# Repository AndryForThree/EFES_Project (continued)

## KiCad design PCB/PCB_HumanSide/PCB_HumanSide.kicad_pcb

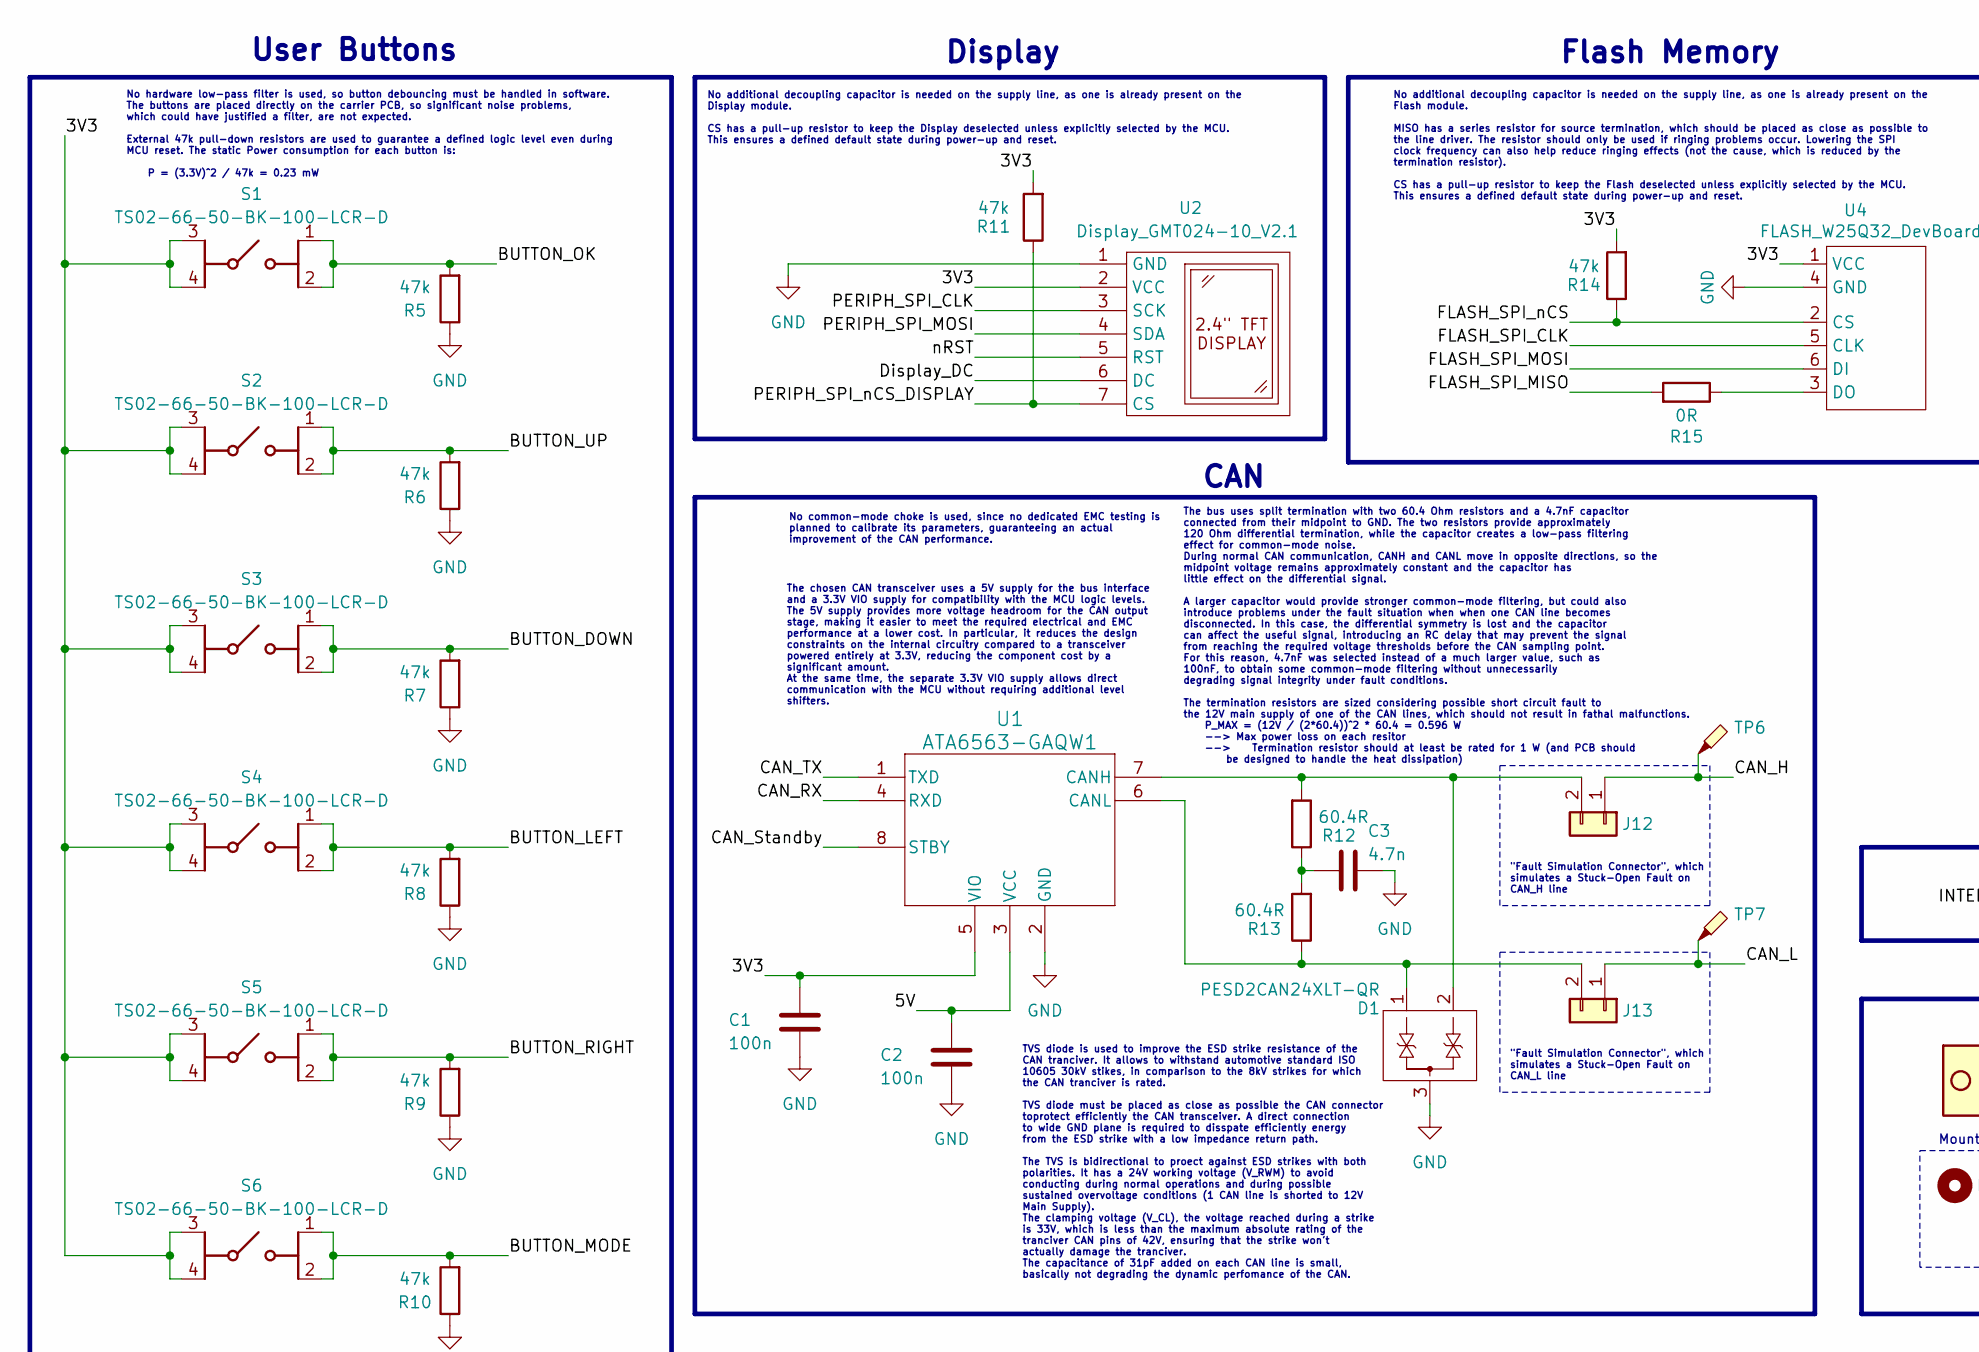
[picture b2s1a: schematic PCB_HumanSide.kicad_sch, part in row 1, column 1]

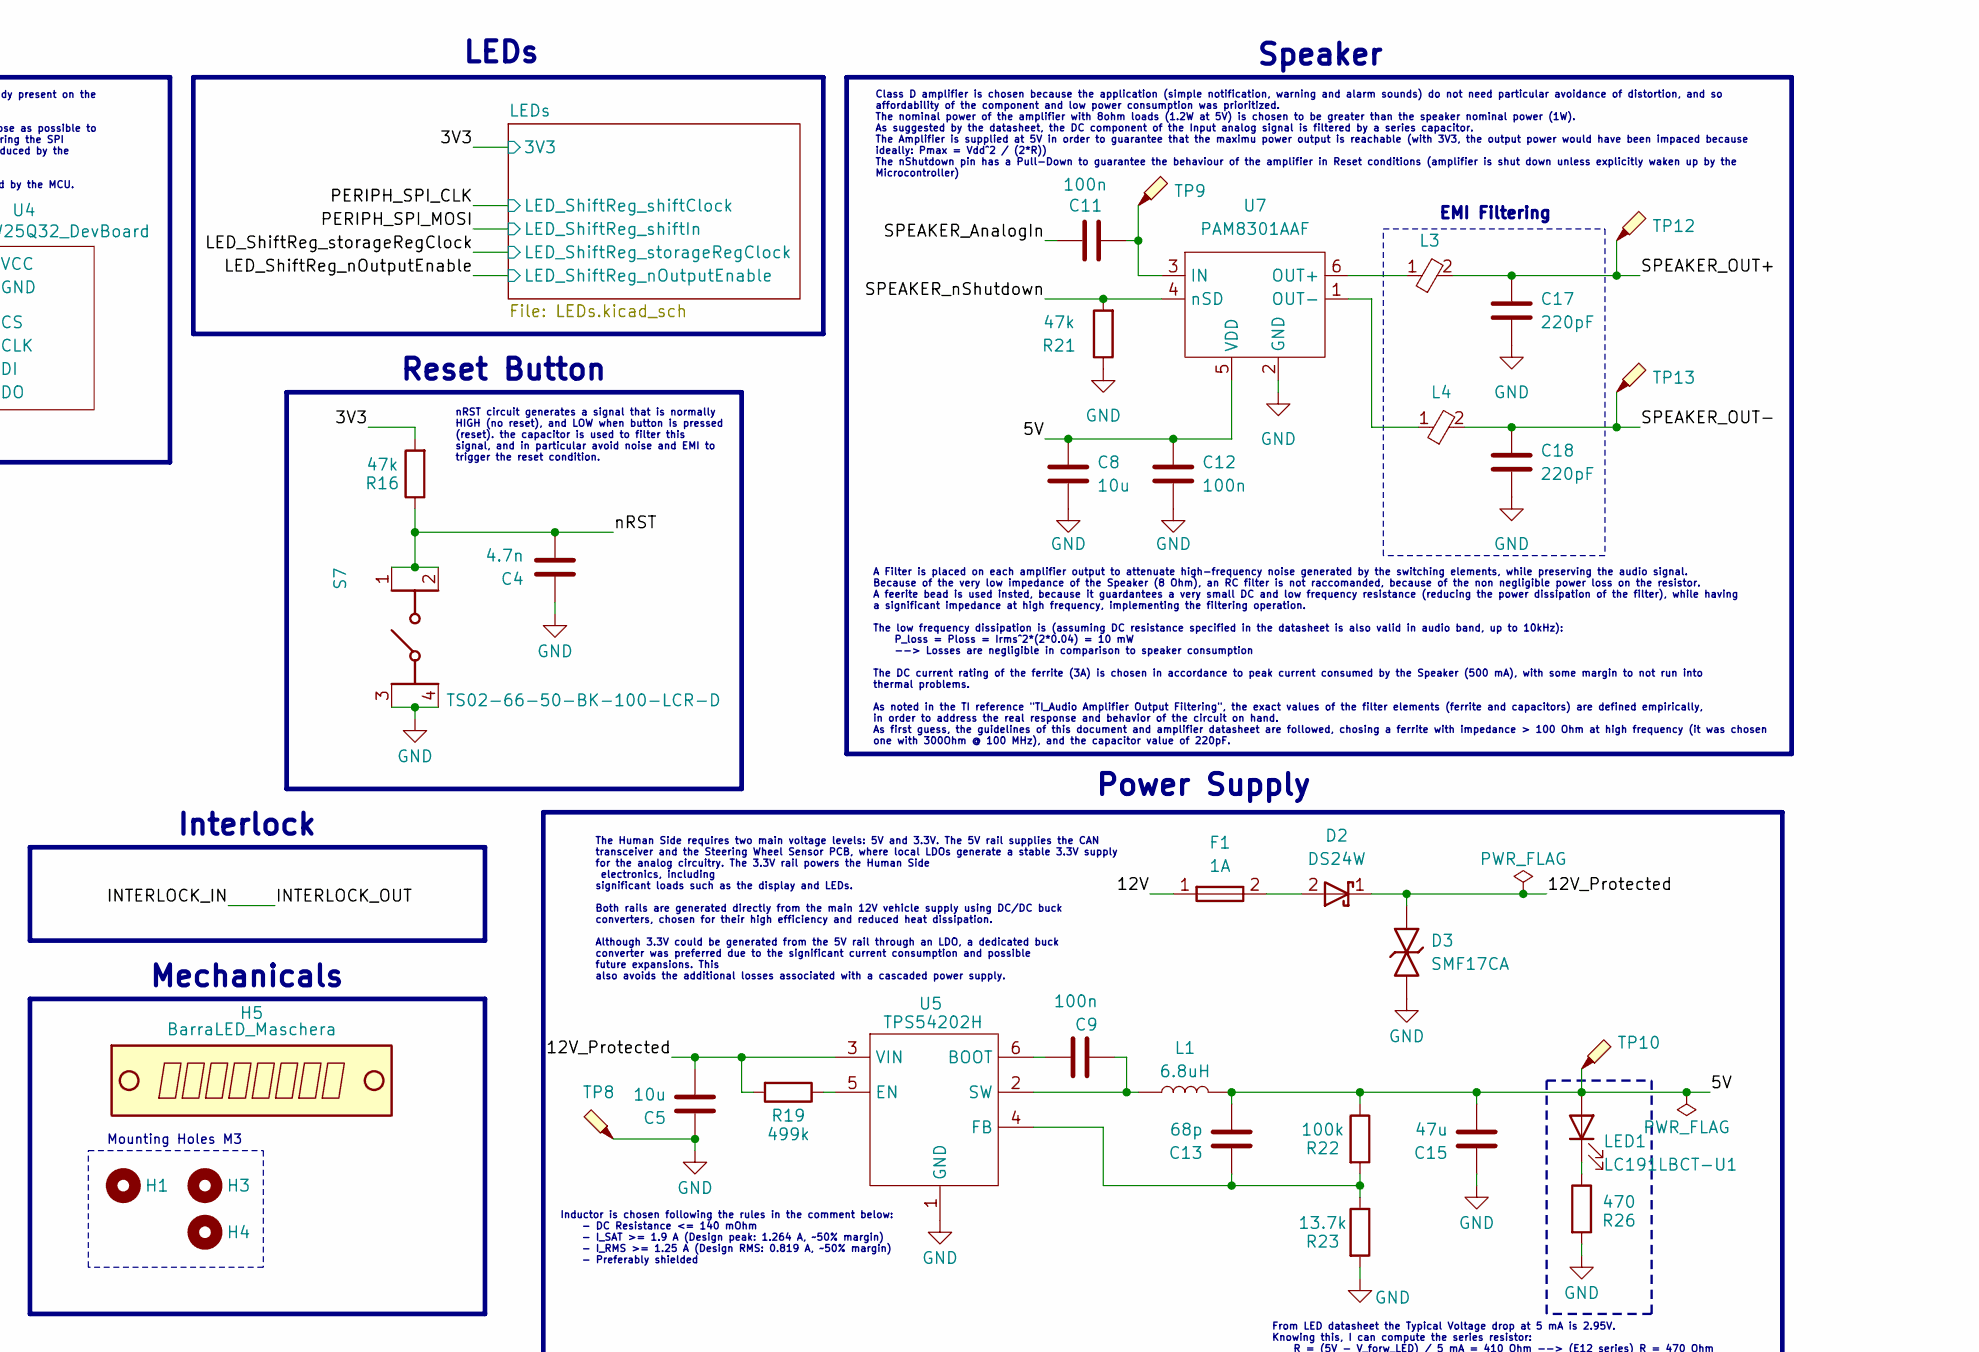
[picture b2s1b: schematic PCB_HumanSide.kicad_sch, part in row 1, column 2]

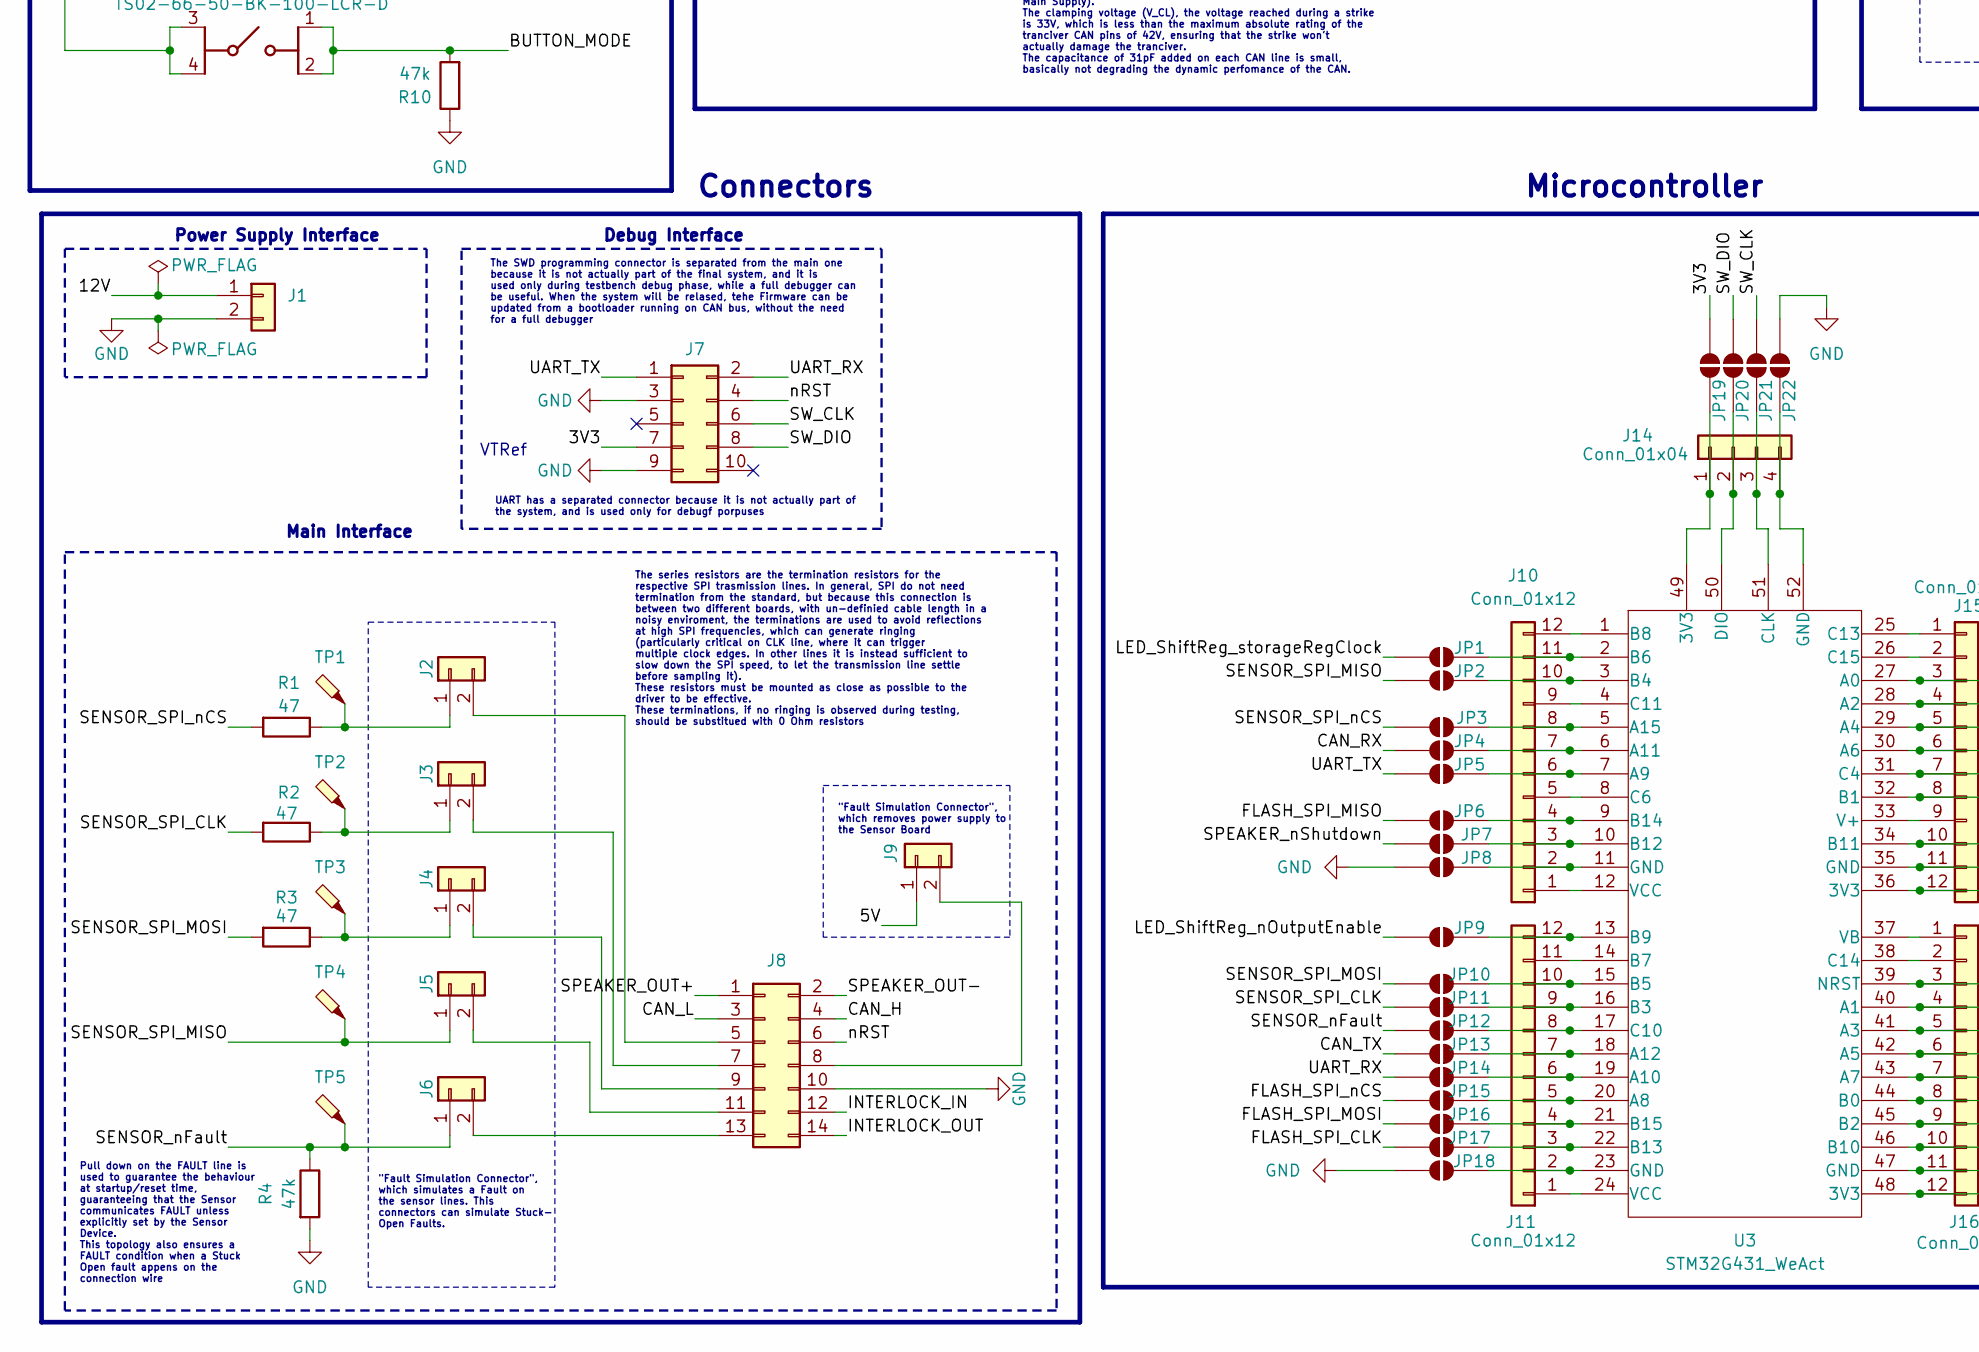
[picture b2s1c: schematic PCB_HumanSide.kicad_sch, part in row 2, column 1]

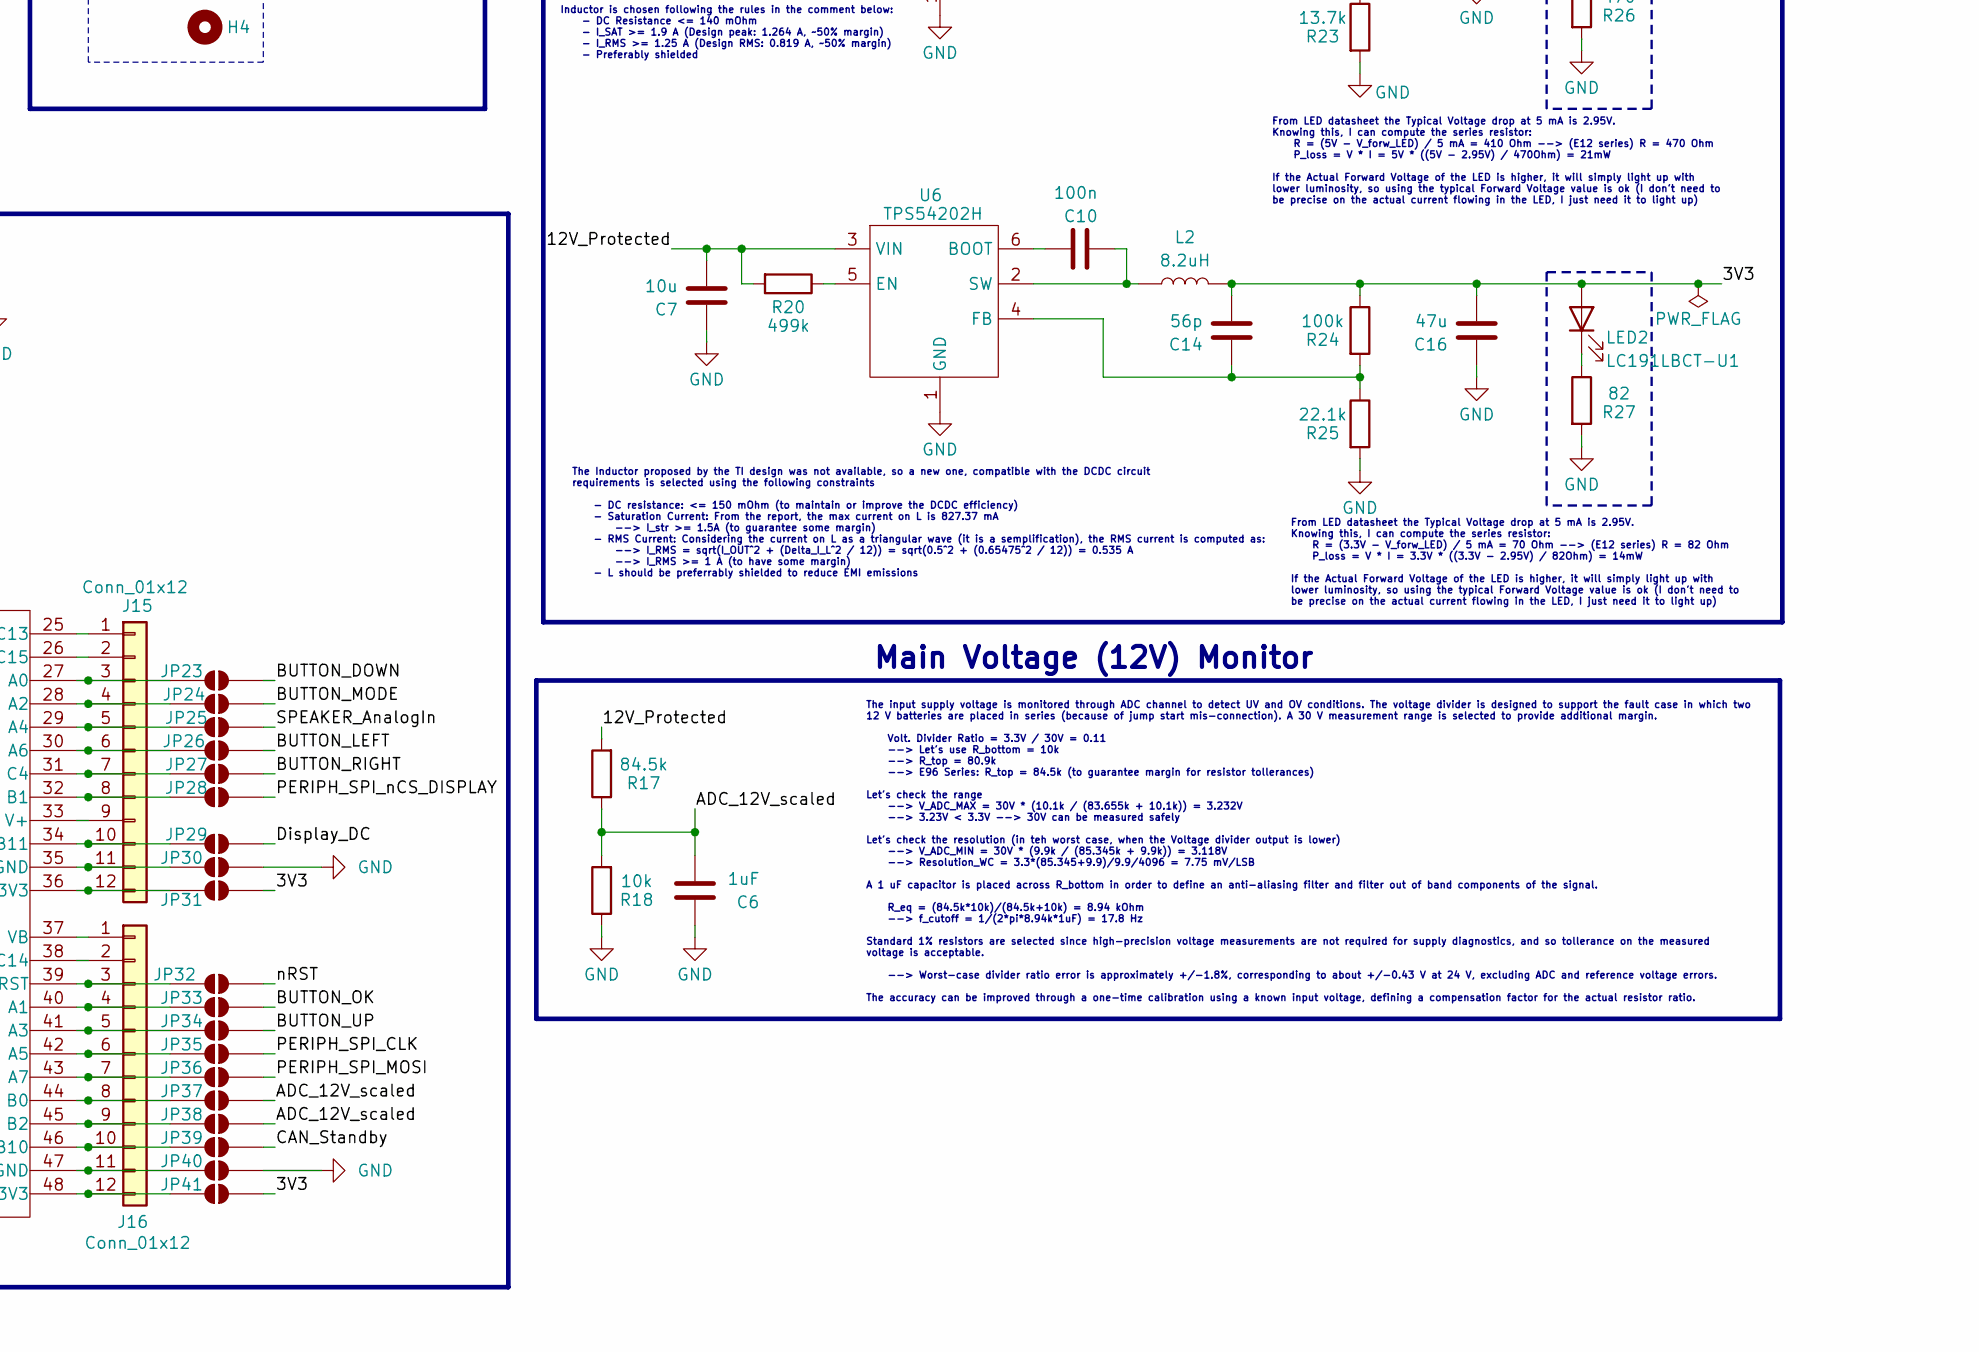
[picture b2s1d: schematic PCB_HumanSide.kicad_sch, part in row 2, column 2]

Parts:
C1, C2, C9, C10, C11, C12: 100n; C_0805_2012Metric_Pad1.18x1.45mm_HandSolder
C3, C4: 4.7n; C_0805_2012Metric_Pad1.18x1.45mm_HandSolder
C5, C7: 10u; C_1206_3216Metric_Pad1.33x1.80mm_HandSolder
C6: 1uF; C_0805_2012Metric_Pad1.18x1.45mm_HandSolder
C8: 10u; C_0805_2012Metric_Pad1.18x1.45mm_HandSolder
C13: 68p; C_0805_2012Metric_Pad1.18x1.45mm_HandSolder
C14: 56p; C_0805_2012Metric_Pad1.18x1.45mm_HandSolder
C15, C16: 47u; C_1206_3216Metric_Pad1.33x1.80mm_HandSolder
C17, C18: 220pF; C_0805_2012Metric_Pad1.18x1.45mm_HandSolder
D1: PESD2CAN24XLT-QR; SOT-23
D2: DS24W; SOD-123_HandSolder
D3: SMF17CA; SOD-123_Bidirectional_HandSolder
F1: 1A; Fuse_1206_3216Metric_Pad1.42x1.75mm_HandSolder
H1, H3, H4: MountingHole; MountingHole_3.2mm_M3
H5: BarraLED_Maschera
J1: TAD05-02-1-L-G; CONN_TAD05-02-1-L-G
J2, J3, J4, J5, J6: Conn_01x03; PinHeader_1x02_P2.54mm_Vertical
J7: SBH11-PBPC-D05-RA-BK; CONN_SBH11-PBPC-D05-RA-BK
J8: SBH11-PBPC-D07-RA-BK; CONN_SBH11-PBPC-D07-RA-BK
J9: Conn_01x02; PinHeader_1x02_P2.54mm_Vertical
J10, J11, J15, J16: Conn_01x12; PinSocket_1x12_P2.54mm_Vertical_TightCourtyard
J12, J13: Conn_01x05; PinHeader_1x02_P2.54mm_Vertical
J14: Conn_01x04; PinSocket_1x04_P2.54mm_Vertical
JP1, JP2, JP3, JP4, JP5, JP6, JP7, JP8, JP9, JP10, JP11, JP12, JP13, JP14, JP15, JP16, JP17, JP18, JP23, JP24, JP25, JP26, JP27, JP28, JP29, JP30, JP31, JP32, JP33, JP34, JP35, JP36, JP37, JP38, JP39, JP40, JP41: SolderBride_0603
JP19, JP20, JP21, JP22: SolderJumper_2_Open; SolderBride_0603
L1: 6.8uH; INDUCT_SRP4020T-6R8M
L2: 8.2uH; INDUCT_CSHB0430R-8R2M
L3, L4: HCB2012KF-301T30; R_0805_2012Metric_Pad1.20x1.40mm_HandSolder
LED1, LED2: LC191LBCT-U1; LED_0603_HandSolder
R1, R2, R3: 47; R_0805_2012Metric_Pad1.20x1.40mm_HandSolder
R4, R5, R6, R7, R8, R9, R10, R11, R14, R16, R21: 47k; R_0805_2012Metric_Pad1.20x1.40mm_HandSolder
R12, R13: 60.4R; R_0805_2012Metric_Pad1.20x1.40mm_HandSolder
R15: 0R; R_0805_2012Metric_Pad1.20x1.40mm_HandSolder
R17: 84.5k; R_0805_2012Metric_Pad1.20x1.40mm_HandSolder
R18: 10k; R_0805_2012Metric_Pad1.20x1.40mm_HandSolder
R19, R20: 499k; R_0805_2012Metric_Pad1.20x1.40mm_HandSolder
R22, R24: 100k; R_0805_2012Metric_Pad1.20x1.40mm_HandSolder
R23: 13.7k; R_0805_2012Metric_Pad1.20x1.40mm_HandSolder
R25: 22.1k; R_0805_2012Metric_Pad1.20x1.40mm_HandSolder
R26: 470; R_0805_2012Metric_Pad1.20x1.40mm_HandSolder
R27: 82; R_0805_2012Metric_Pad1.20x1.40mm_HandSolder
S1, S2, S3, S4, S5, S6, S7: TS02-66-50-BK-100-LCR-D; BUTTON_TS0266100BK100LCRD; Manufacturer_Part_Number TS02-66-50-BK-100-LCR-D; Mouser Part Number 179-TS026650BK100LCR
TP1, TP2, TP3, TP4, TP5, TP6, TP7, TP8, TP9, TP10, TP12, TP13: TestPoint_Probe; TestPoint_Pad_1.5x1.5mm
U1: ATA6563-GAQW1; SOIC8_D_TEX-M
U2: Display_GMT024-10_V2.1
U3: STM32G431_WeAct
U4: FLASH_W25Q32_DevBoard
U5, U6: TPS54202H; SOT-23-6_DBV_TEX-M
U7: PAM8301AAF; SOT-23-6_DBV_TEX-M

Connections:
/3V3: C1.1, C14.2, C16.2, J7.7, JP19.2 (B), JP31.2 (B), JP41.2 (B), L2.2, LED2.2 (A), R11.2, R14.2, R16.2, R24.1, S1.3 (COM_1), S1.4 (COM_2), S2.3 (COM_1), S2.4 (COM_2), S3.3 (COM_1), S3.4 (COM_2), S4.3 (COM_1), S4.4 (COM_2), S5.3 (COM_1), S5.4 (COM_2), S6.3 (COM_1), S6.4 (COM_2), U1.5 (VIO), U2.2 (VCC), U4.1 (VCC); also elsewhere on the board
/5V: C2.1, C8.1, C12.1, C13.2, C15.2, J9.1, L1.2, LED1.2 (A), R22.1, TP10.1 (1_1), U1.3 (VCC), U7.5 (VDD)
/12V: F1.1, J1.1
/12V_Protected: C5.2, C7.2, D2.1 (K), D3.2 (A), R17.2, R19.2, R20.2, U5.3 (VIN), U6.3 (VIN)
/ADC_12V_scaled: C6.2, JP37.2 (B), JP38.2 (B), R17.1, R18.2
/BUTTON_DOWN: JP23.2 (B), R7.2, S3.1 (NO_1), S3.2 (NO_2)
/BUTTON_LEFT: JP26.1 (A), R8.2, S4.1 (NO_1), S4.2 (NO_2)
/BUTTON_MODE: JP24.1 (A), R10.2, S6.1 (NO_1), S6.2 (NO_2)
/BUTTON_OK: JP33.2 (B), R5.2, S1.1 (NO_1), S1.2 (NO_2)
/BUTTON_RIGHT: JP27.1 (A), R9.2, S5.1 (NO_1), S5.2 (NO_2)
/BUTTON_UP: JP34.2 (B), R6.2, S2.1 (NO_1), S2.2 (NO_2)
/CAN_H: J8.4, J12.1, TP6.1 (1_1)
/CAN_L: J8.3, J13.1, TP7.1 (1_1)
/CAN_RX: JP4.1 (A), U1.4 (RXD)
/CAN_Standby: JP39.1 (A), U1.8 (STBY)
/CAN_TX: JP13.1 (A), U1.1 (TXD)
/Display_DC: JP29.1 (A), U2.6 (DC)
/FLASH_SPI_CLK: JP17.1 (A), U4.5 (CLK)
/FLASH_SPI_MISO: JP6.1 (A), R15.2
/FLASH_SPI_MOSI: JP16.1 (A), U4.6 (DI)
/FLASH_SPI_nCS: JP15.1 (A), R14.1, U4.2 (CS)
/INTERLOCK_IN: J8.12 (Pin_10), J8.14 (Pin_10)
/LED_ShiftReg_nOutputEnable: JP9.1 (A); also elsewhere on the board
/LED_ShiftReg_storageRegClock: JP1.1 (A); also elsewhere on the board
/PERIPH_SPI_CLK: JP35.2 (B), U2.3 (SCK); also elsewhere on the board
/PERIPH_SPI_MOSI: JP36.2 (B), U2.4 (SDA); also elsewhere on the board
/PERIPH_SPI_nCS_DISPLAY: JP28.1 (A), R11.1, U2.7 (CS)
/SENSOR_SPI_CLK: JP11.1 (A), R2.2
/SENSOR_SPI_MISO: J5.1, JP2.1 (A), TP4.1 (1_1)
/SENSOR_SPI_MOSI: JP10.1 (A), R3.2
/SENSOR_SPI_nCS: JP3.1 (A), R1.2
/SENSOR_nFault: J6.1, JP12.1 (A), R4.1, TP5.1 (1_1)
/SPEAKER_AnalogIn: C11.1, JP25.1 (A)
/SPEAKER_OUT+: C17.1, J8.1, L3.2, TP12.1 (1_1)
/SPEAKER_OUT-: C18.1, J8.2, L4.2, TP13.1 (1_1)
/SPEAKER_nShutdown: JP7.2 (B), R21.2, U7.4 (nSD)
/SW_CLK: J7.6, JP21.2 (B)
/SW_DIO: J7.8, JP20.2 (B)
/UART_RX: J7.2, JP14.1 (A)
/UART_TX: J7.1, JP5.1 (A)
/nRST: C4.2, J7.4, J8.6, JP32.2 (B), R16.1, S7.1 (NO_1), S7.2 (NO_2), U2.5 (RST)
GND: C1.2, C2.2, C3.2, C4.1, C5.1, C6.1, C7.1, C8.2, C12.2, C15.1, C16.1, C17.2, C18.2, D1.3 (COM), D3.1 (K), J1.2, J7.3, J7.9, J8.10, JP8.2 (B), JP18.2 (B), JP22.2 (B), JP30.2 (B), JP40.2 (B), R4.2, R5.1, R6.1, R7.1, R8.1, R9.1, R10.1, R18.1, R21.1, R23.2, R25.2, R26.2, R27.2, S7.3 (COM_1), S7.4 (COM_2), TP8.1 (1_1), U1.2 (GND), U2.1 (GND), U4.4 (GND), U5.1 (GND), U6.1 (GND), U7.2 (GND); also elsewhere on the board
unnamed: C3.1, R12.1, R13.2
unnamed: D1.1 (K1), J13.2, R13.1, U1.6 (CANL)
unnamed: D1.2 (K2), J12.2, R12.2, U1.7 (CANH)
unnamed: D2.2 (A), F1.2
unnamed: J2.1, R1.1, TP1.1 (1_1)
unnamed: J2.2, J8.5
unnamed: J3.1, R2.1, TP2.1 (1_1)
unnamed: J3.2, J8.7
unnamed: J4.1, R3.1, TP3.1 (1_1)
unnamed: J4.2, J8.9
unnamed: J5.2, J8.11 (Pin_9)
unnamed: J6.2, J8.13 (Pin_9)
unnamed: J8.8, J9.2
unnamed: J10.1, U3.12 (VCC)
unnamed: J10.2, JP8.1 (A), U3.11 (GND)
unnamed: J10.3, JP7.1 (A), U3.10 (B12)
unnamed: J10.4, JP6.2 (B), U3.9 (B14)
unnamed: J10.5, U3.8 (C6)
unnamed: J10.6, JP5.2 (B), U3.7 (A9)
unnamed: J10.7, JP4.2 (B), U3.6 (A11)
unnamed: J10.8, JP3.2 (B), U3.5 (A15)
unnamed: J10.9, U3.4 (C11)
unnamed: J10.10, JP2.2 (B), U3.3 (B4)
unnamed: J10.11, JP1.2 (B), U3.2 (B6)
unnamed: J10.12, U3.1 (B8)
unnamed: J11.1, U3.24 (VCC)
unnamed: J11.2, JP18.1 (A), U3.23 (GND)
unnamed: J11.3, JP17.2 (B), U3.22 (B13)
unnamed: J11.4, JP16.2 (B), U3.21 (B15)
unnamed: J11.5, JP15.2 (B), U3.20 (A8)
unnamed: J11.6, JP14.2 (B), U3.19 (A10)
unnamed: J11.7, JP13.2 (B), U3.18 (A12)
unnamed: J11.8, JP12.2 (B), U3.17 (C10)
unnamed: J11.9, JP11.2 (B), U3.16 (B3)
unnamed: J11.10, JP10.2 (B), U3.15 (B5)
unnamed: J11.11, U3.14 (B7)
unnamed: J11.12, JP9.2 (B), U3.13 (B9)
unnamed: J14.1, JP19.1 (A), U3.49 (3V3)
unnamed: J14.2, JP20.1 (A), U3.50 (DIO)
unnamed: J14.3, JP21.1 (A), U3.51 (CLK)
unnamed: J14.4, JP22.1 (A), U3.52 (GND)
unnamed: J15.1, U3.25 (C13)
unnamed: J15.2, U3.26 (C15)
unnamed: J15.3, JP23.1 (A), U3.27 (A0)
unnamed: J15.4, JP24.2 (B), U3.28 (A2)
unnamed: J15.5, JP25.2 (B), U3.29 (A4)
unnamed: J15.6, JP26.2 (B), U3.30 (A6)
unnamed: J15.7, JP27.2 (B), U3.31 (C4)
unnamed: J15.8, JP28.2 (B), U3.32 (B1)
unnamed: J15.9, U3.33 (V+)
unnamed: J15.10, JP29.2 (B), U3.34 (B11)
unnamed: J15.11, JP30.1 (A), U3.35 (GND)
unnamed: J15.12, JP31.1 (A), U3.36 (3V3)
unnamed: J16.1, U3.37 (VB)
unnamed: J16.2, U3.38 (C14)
unnamed: J16.3, JP32.1 (A), U3.39 (NRST)
unnamed: J16.4, JP33.1 (A), U3.40 (A1)
unnamed: J16.5, JP34.1 (A), U3.41 (A3)
unnamed: J16.6, JP35.1 (A), U3.42 (A5)
unnamed: J16.7, JP36.1 (A), U3.43 (A7)
unnamed: J16.8, JP37.1 (A), U3.44 (B0)
unnamed: J16.9, JP38.1 (A), U3.45 (B2)
unnamed: J16.10, JP39.2 (B), U3.46 (B10)
unnamed: J16.11, JP40.1 (A), U3.47 (GND)
unnamed: J16.12, JP41.1 (A), U3.48 (3V3)
unnamed: LED1.1 (K), R26.1
unnamed: LED2.1 (K), R27.1
unnamed: R15.1, U4.3 (DO)
unnamed: C9.1, U5.6 (BOOT)
unnamed: R19.1, U5.5 (EN)
unnamed: C13.1, R22.2, R23.1, U5.4 (FB)
unnamed: C9.2, L1.1, U5.2 (SW)
unnamed: C10.1, U6.6 (BOOT)
unnamed: R20.1, U6.5 (EN)
unnamed: C14.1, R24.2, R25.1, U6.4 (FB)
unnamed: C10.2, L2.1, U6.2 (SW)
unnamed: C11.2, TP9.1 (1_1), U7.3 (IN)
unnamed: L3.1, U7.6 (OUT+)
unnamed: L4.1, U7.1 (OUT-)

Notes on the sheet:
Microcontroller
Power Supply
Pull down on the FAULT line is used to guarantee the behaviour at startup/reset time, guaranteeing that the Sensor communicates FAULT unless explicitly set by the Sensor Device. This topology also ensures a FAULT condition when a Stuck Open fault appens on the connection wire
No additional decoupling capacitor is needed on the supply line, as one is already present on the Flash module. MISO has a series resistor for source termination, which should be placed as close as possible to the line driver. The resistor should only be used if ringing problems occur. Lowering the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
The SWD programming connector is separated from the main one because it is not actually part of the final system, and it is used only during testbench debug phase, while a full debugger can be useful. When the system will be relased, tehe Firmware can be updated from a bootloader running on CAN bus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
LEDs
"Fault Simulation Connector", which simulates a Fault on the sensor lines. This connectors can simulate Stuck- Open Faults.
"Fault Simulation Connector", which simulates a Stuck-Open Fault on CAN_H line
CAN
No hardware low-pass filter is used, so button debouncing must be handled in software. The buttons are placed directly on the carrier PCB, so significant noise problems, which could have justified a filter, are not expected. External 47k pull-down resistors are used to guarantee a defined logic lev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
nRST circuit generates a signal that is normally HIGH (no reset), and LOW when button is pressed (reset). the capacitor is used to filter this signal, and in particular avoid noise and EMI to trigger the reset condition.
EMI Filtering
Display
VTRef
The input supply voltage is monitored through ADC channel to detect UV and OV conditions. The voltage divider is designed to support the fault case in which two 12 V batteries are placed in series (because of jump start mis-connection). A 30 V measurement range is selected to provide additional mar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
Interlock
The bus uses split termination with two 60.4 Ohm resistors and a 4.7nF capacitor connected from their midpoint to GND. The two resistors provide approximately 120 Ohm differential termination, while the capacitor creates a low-pass filtering effect for common-mode noise. During normal CAN communica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
No common-mode choke is used, since no dedicated EMC testing is planned to calibrate its parameters, guaranteeing an actual improvement of the CAN performance.
Connectors
The chosen CAN transceiver uses a 5V supply for the bus interface and a 3.3V VIO supply for compatibility with the MCU logic levels. The 5V supply provides more voltage headroom for the CAN output stage, making it easier to meet the required electrical and EMC performance at a lower cost. In partic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
The series resistors are the termination resistors for the respective SPI trasmission lines. In general, SPI do not need termination from the standard, but because this connection is between two different boards, with un-definied cable length in a noisy enviroment, the terminations are used to avoi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
Main Voltage (12V) Monitor
Flash Memory
From LED datasheet the Typical Voltage drop at 5 mA is 2.95V. Knowing this, I can compute the series resistor: R = (5V - V_forw_LED) / 5 mA = 410 Ohm --> (E12 series) R = 470 Ohm P_loss = V * I = 5V * ((5V - 2.95V) / 470Ohm) = 21mW If the Actual Forward Voltage of the LED is higher, it will simply 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
Class D amplifier is chosen because the application (simple notification, warning and alarm sounds) do not need particular avoidance of distortion, and so affordability of the component and low power consumption was prioritized. The nominal power of the amplifier with 8ohm loads (1.2W at 5V) is cho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
Speaker
Mounting Holes M3
UART has a separated connector because it is not actually part of the system, and is used only for debugf porpuses
"Fault Simulation Connector", which simulates a Stuck-Open Fault on CAN_L line
The Human Side requires two main voltage levels: 5V and 3.3V. The 5V rail supplies the CAN transceiver and the Steering Wheel Sensor PCB, where local LDOs generate a stable 3.3V supply for the analog circuitry. The 3.3V rail powers the Human Side electronics, including significant loads such as the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
"Fault Simulation Connector", which removes power supply to the Sensor Board
No additional decoupling capacitor is needed on the supply line, as one is already present on the Display module. CS has a pull-up resistor to keep the Display deselected unless explicitly selected by the MCU. This ensures a defined default state during power-up and reset.
Debug Interface
User Buttons
Main Interface
A Filter is placed on each amplifier output to attenuate high-frequency noise generated by the switching elements, while preserving the audio signal. Because of the very low impedance of the Speaker (8 Ohm), an RC filter is not raccomanded, because of the non negligible power loss on the resistor. 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
Inductor is chosen following the rules in the comment below: - DC Resistance <= 140 mOhm - I_SAT >= 1.9 A (Design peak: 1.264 A, ~50% margin) - I_RMS >= 1.25 A (Design RMS: 0.819 A, ~50% margin) - Preferably shielded
TVS diode is used to improve the ESD strike resistance of the CAN tranciver. It allows to withstand automotive standard ISO 10605 30kV stikes, in comparison to the 8kV strikes for which the CAN tranciver is rated. TVS diode must be placed as close as possible the CAN connector toprotect efficiently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
Reset Button
Mechanicals

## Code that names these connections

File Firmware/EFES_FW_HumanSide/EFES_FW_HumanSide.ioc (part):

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Mcu.Name=STM32G431C(6-8-B)Ux
Mcu.Package=UFQFPN48
Mcu.UserName=STM32G431CBUx
PA0.GPIOParameters=GPIO_Label
PA0.GPIO_Label=BUTTON_DOWN
PA0.Signal=GPXTI0
PA1.GPIOParameters=GPIO_Label
PA1.GPIO_Label=BUTTON_OK
PA1.Signal=GPXTI1
PA10.Mode=Asynchronous
PA10.Signal=USART1_RX
PA11.Mode=FDCAN_Activate
PA11.Signal=FDCAN1_RX
PA12.Mode=FDCAN_Activate
PA12.Signal=FDCAN1_TX
PA13.Mode=Serial_Wire
PA13.Signal=SYS_JTMS-SWDIO
PA14.Mode=Serial_Wire
PA14.Signal=SYS_JTCK-SWCLK
PA15.GPIOParameters=GPIO_Label
PA15.GPIO_Label=SENSOR_SPI_nCS
PA15.Signal=GPIO_Output
PA2.GPIOParameters=GPIO_Label
PA2.GPIO_Label=BUTTON_MODE
PA2.Signal=GPXTI2
PA3.GPIOParameters=GPIO_Label
PA3.GPIO_Label=BUTTON_UP
PA3.Signal=GPXTI3
PA4.Signal=COMP_DAC11_group
PA5.Mode=Simplex_Bidirectional_Master
PA5.Signal=SPI1_SCK
PA6.GPIOParameters=GPIO_Label
PA6.GPIO_Label=BUTTON_LEFT
PA6.Signal=GPXTI6
PA7.Mode=Simplex_Bidirectional_Master
PA7.Signal=SPI1_MOSI
PA8.GPIOParameters=GPIO_Label
PA8.GPIO_Label=FLASH_SPI_nCS
PA8.Signal=GPIO_Output
PA9.Mode=Asynchronous
PA9.Signal=USART1_TX
PB0.Mode=INP
PB0.Signal=COMP4_INP
PB1.GPIOParameters=GPIO_Label
PB1.GPIO_Label=PERIPH_SPI_nCS_DISPLAY
PB1.Signal=GPIO_Output
PB10.GPIOParameters=GPIO_Label
PB10.GPIO_Label=CAN_Standby
PB10.Signal=GPIO_Output
PB11.GPIOParameters=GPIO_Label
PB11.GPIO_Label=Display_DC
PB11.Signal=GPIO_Output
PB12.GPIOParameters=GPIO_Label
PB12.GPIO_Label=SPEAKER_nShutdown
PB12.Signal=GPIO_Output
PB13.Mode=Full_Duplex_Master
PB13.Signal=SPI2_SCK
PB14.Mode=Full_Duplex_Master
PB14.Signal=SPI2_MISO
PB15.Mode=Full_Duplex_Master
PB15.Signal=SPI2_MOSI
PB2.Mode=IN12-Single-Ended
PB2.Signal=ADC2_IN12
PB3.Mode=Full_Duplex_Master
PB3.Signal=SPI3_SCK
PB4.Mode=Full_Duplex_Master
PB4.Signal=SPI3_MISO
PB5.Mode=Full_Duplex_Master
PB5.Signal=SPI3_MOSI
PB6.GPIOParameters=GPIO_Label
PB6.GPIO_Label=LED_ShiftReg_storageRegClock
PB6.Signal=GPIO_Output
PB9.Signal=S_TIM17_CH1
PC10.GPIOParameters=GPIO_Label
PC10.GPIO_Label=SENSOR_nFault
PC10.Signal=GPIO_Input
PC4.GPIOParameters=GPIO_Label
PC4.GPIO_Label=BUTTON_RIGHT
PC4.Signal=GPXTI4
PC6.GPIOParameters=GPIO_Label
PC6.GPIO_Label=Board_LED
PC6.Signal=GPIO_Output
PF0-OSC_IN.Mode=HSE-External-Oscillator
PF0-OSC_IN.Signal=RCC_OSC_IN
PF1-OSC_OUT.Mode=HSE-External-Oscillator
PF1-OSC_OUT.Signal=RCC_OSC_OUT
RCC.HSE_VALUE=8000000
RCC.SYSCLKFreq_VALUE=168000000
RCC.SYSCLKSource=RCC_SYSCLKSOURCE_PLLCLK
board=custom

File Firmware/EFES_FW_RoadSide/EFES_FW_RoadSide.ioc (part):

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Mcu.Name=STM32G431C(6-8-B)Ux
Mcu.Package=UFQFPN48
Mcu.UserName=STM32G431CBUx
PA0.GPIOParameters=GPIO_Label
PA0.GPIO_Label=ADC_12V_Motor_scaled
PA0.Mode=IN1-Single-Ended
PA0.Signal=ADC2_IN1
PA10.Mode=Asynchronous
PA10.Signal=USART1_RX
PA11.Mode=FDCAN_Activate
PA11.Signal=FDCAN1_RX
PA12.Mode=FDCAN_Activate
PA12.Signal=FDCAN1_TX
PA13.Mode=Serial_Wire
PA13.Signal=SYS_JTMS-SWDIO
PA14.Mode=Serial_Wire
PA14.Signal=SYS_JTCK-SWCLK
PA2.GPIOParameters=GPIO_Label,GPIO_ModeDefaultEXTI,GPIO_PuPd
PA2.GPIO_Label=DRV8874_FAULT
PA2.GPIO_ModeDefaultEXTI=GPIO_MODE_IT_FALLING
PA2.GPIO_PuPd=GPIO_NOPULL
PA2.Signal=GPXTI2
PA4.GPIOParameters=GPIO_Label,GPIO_ModeDefaultOutputPP,PinState,GPIO_PuPd
PA4.GPIO_Label=DRV8874_PMODE
PA4.GPIO_ModeDefaultOutputPP=GPIO_MODE_OUTPUT_PP
PA4.GPIO_PuPd=GPIO_NOPULL
PA4.PinState=GPIO_PIN_RESET
PA4.Signal=GPIO_Output
PA6.Mode=IN3-Single-Ended
PA6.Signal=ADC2_IN3
PA7.GPIOParameters=GPIO_Label
PA7.GPIO_Label=HBRIDGE_PWM_VrefControl
PA7.Signal=S_TIM3_CH2
PA9.Mode=Asynchronous
PA9.Signal=USART1_TX
PB0.GPIOParameters=GPIO_Label
PB0.GPIO_Label=HBRIDGE_EN_IN1
PB0.Signal=S_TIM3_CH3
PB1.GPIOParameters=GPIO_Label
PB1.GPIO_Label=HBRIDGE_PH_IN2
PB1.Signal=S_TIM3_CH4
PB11.GPIOParameters=GPIO_Label,GPIO_ModeDefaultOutputPP,PinState,GPIO_PuPd
PB11.GPIO_Label=DRV8874_SLEEP
PB11.GPIO_ModeDefaultOutputPP=GPIO_MODE_OUTPUT_OD
PB11.GPIO_PuPd=GPIO_NOPULL
PB11.PinState=GPIO_PIN_RESET
PB11.Signal=GPIO_Output
PB12.GPIOParameters=GPIO_Label
PB12.GPIO_Label=ADC_VehicleSpeed_Filtered
PB12.Mode=IN11-Single-Ended
PB12.Signal=ADC1_IN11
PB14.GPIOParameters=GPIO_Label
PB14.GPIO_Label=ADC_MotorPosition_Filtered
PB14.Mode=IN5-Single-Ended
PB14.Signal=ADC1_IN5
PB3.GPIOParameters=GPIO_Label
PB3.GPIO_Label=CAN_Standby
PB3.Signal=GPIO_Output
PB4.GPIOParameters=GPIO_Label,GPIO_ModeDefaultOutputPP,PinState,GPIO_PuPd
PB4.GPIO_Label=LED_FAULT
PB4.GPIO_ModeDefaultOutputPP=GPIO_MODE_OUTPUT_PP
PB4.GPIO_PuPd=GPIO_NOPULL
PB4.PinState=GPIO_PIN_RESET
PB4.Signal=GPIO_Output
PB5.GPIOParameters=GPIO_Label,GPIO_PuPd
PB5.GPIO_Label=INTERLOCK_RELAY_CMD
PB5.GPIO_PuPd=GPIO_NOPULL
PB5.Signal=GPIO_Input
PB6.GPIOParameters=GPIO_Label,GPIO_ModeDefaultOutputPP,PinState,GPIO_PuPd
PB6.GPIO_Label=LED_ALIVE
PB6.GPIO_ModeDefaultOutputPP=GPIO_MODE_OUTPUT_PP
PB6.GPIO_PuPd=GPIO_NOPULL
PB6.PinState=GPIO_PIN_RESET
PB6.Signal=GPIO_Output
PB7.GPIOParameters=GPIO_Label,GPIO_ModeDefaultOutputPP,PinState,GPIO_PuPd
PB7.GPIO_Label=LED_MOTOR_ENABLE
PB7.GPIO_ModeDefaultOutputPP=GPIO_MODE_OUTPUT_PP
PB7.GPIO_PuPd=GPIO_NOPULL
PB7.PinState=GPIO_PIN_RESET
PB7.Signal=GPIO_Output
PC6.GPIOParameters=GPIO_Label
PC6.GPIO_Label=Board_LED
PC6.Signal=GPIO_Output
PF0-OSC_IN.Mode=HSE-External-Oscillator
PF0-OSC_IN.Signal=RCC_OSC_IN
PF1-OSC_OUT.Mode=HSE-External-Oscillator
PF1-OSC_OUT.Signal=RCC_OSC_OUT
RCC.HSE_VALUE=8000000
RCC.SYSCLKFreq_VALUE=168000000
RCC.SYSCLKSource=RCC_SYSCLKSOURCE_PLLCLK
board=custom
